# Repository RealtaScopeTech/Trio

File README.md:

# Trio
Realta Scope Tech: Trio Focuser

# What is it?

The REALTA Trio is a device that can control dew heaters, distribute 12 volt power and is an ASCOM compatible focuser. 

# Why did you make it?

The cost of some auxiliary astronomy equipment is crazy. I had no intention of paying $100 for a device the controls dew heaters via simple pulse width modulation, another $100 on a box that connects red and black wires to distribute 12v power and $200+ on a focuser controller. The cost saving plus the potential to learn something really intrigued me and the amount of information/free tools and general advice available to help people make things really inspired me, it's just astounding how useful the internet and open source/hardware have become. 

I also wanted to design something that fitted in a neat case as other maker options had a distinct DIY look to them, I wanted something that looked finished.

# License

Please feel free to make your own copies of the board/cases and ammend their design. Please give credit.

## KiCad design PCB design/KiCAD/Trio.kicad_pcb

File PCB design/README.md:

# PCB Design

The files used to design the PCB can be found in the KiCAD folder.

You may get issues with KiCAD not being able to find custom footprints and 3D models. We have placed all of those used within the KiCAD Extra's folder.

The "Production Files" folder contains all the files need to manufacture the PCB. It includes the Gerber files and a SMD position file and BOM file that can be used with JLCPCB to manufature a board with the SMD components included.

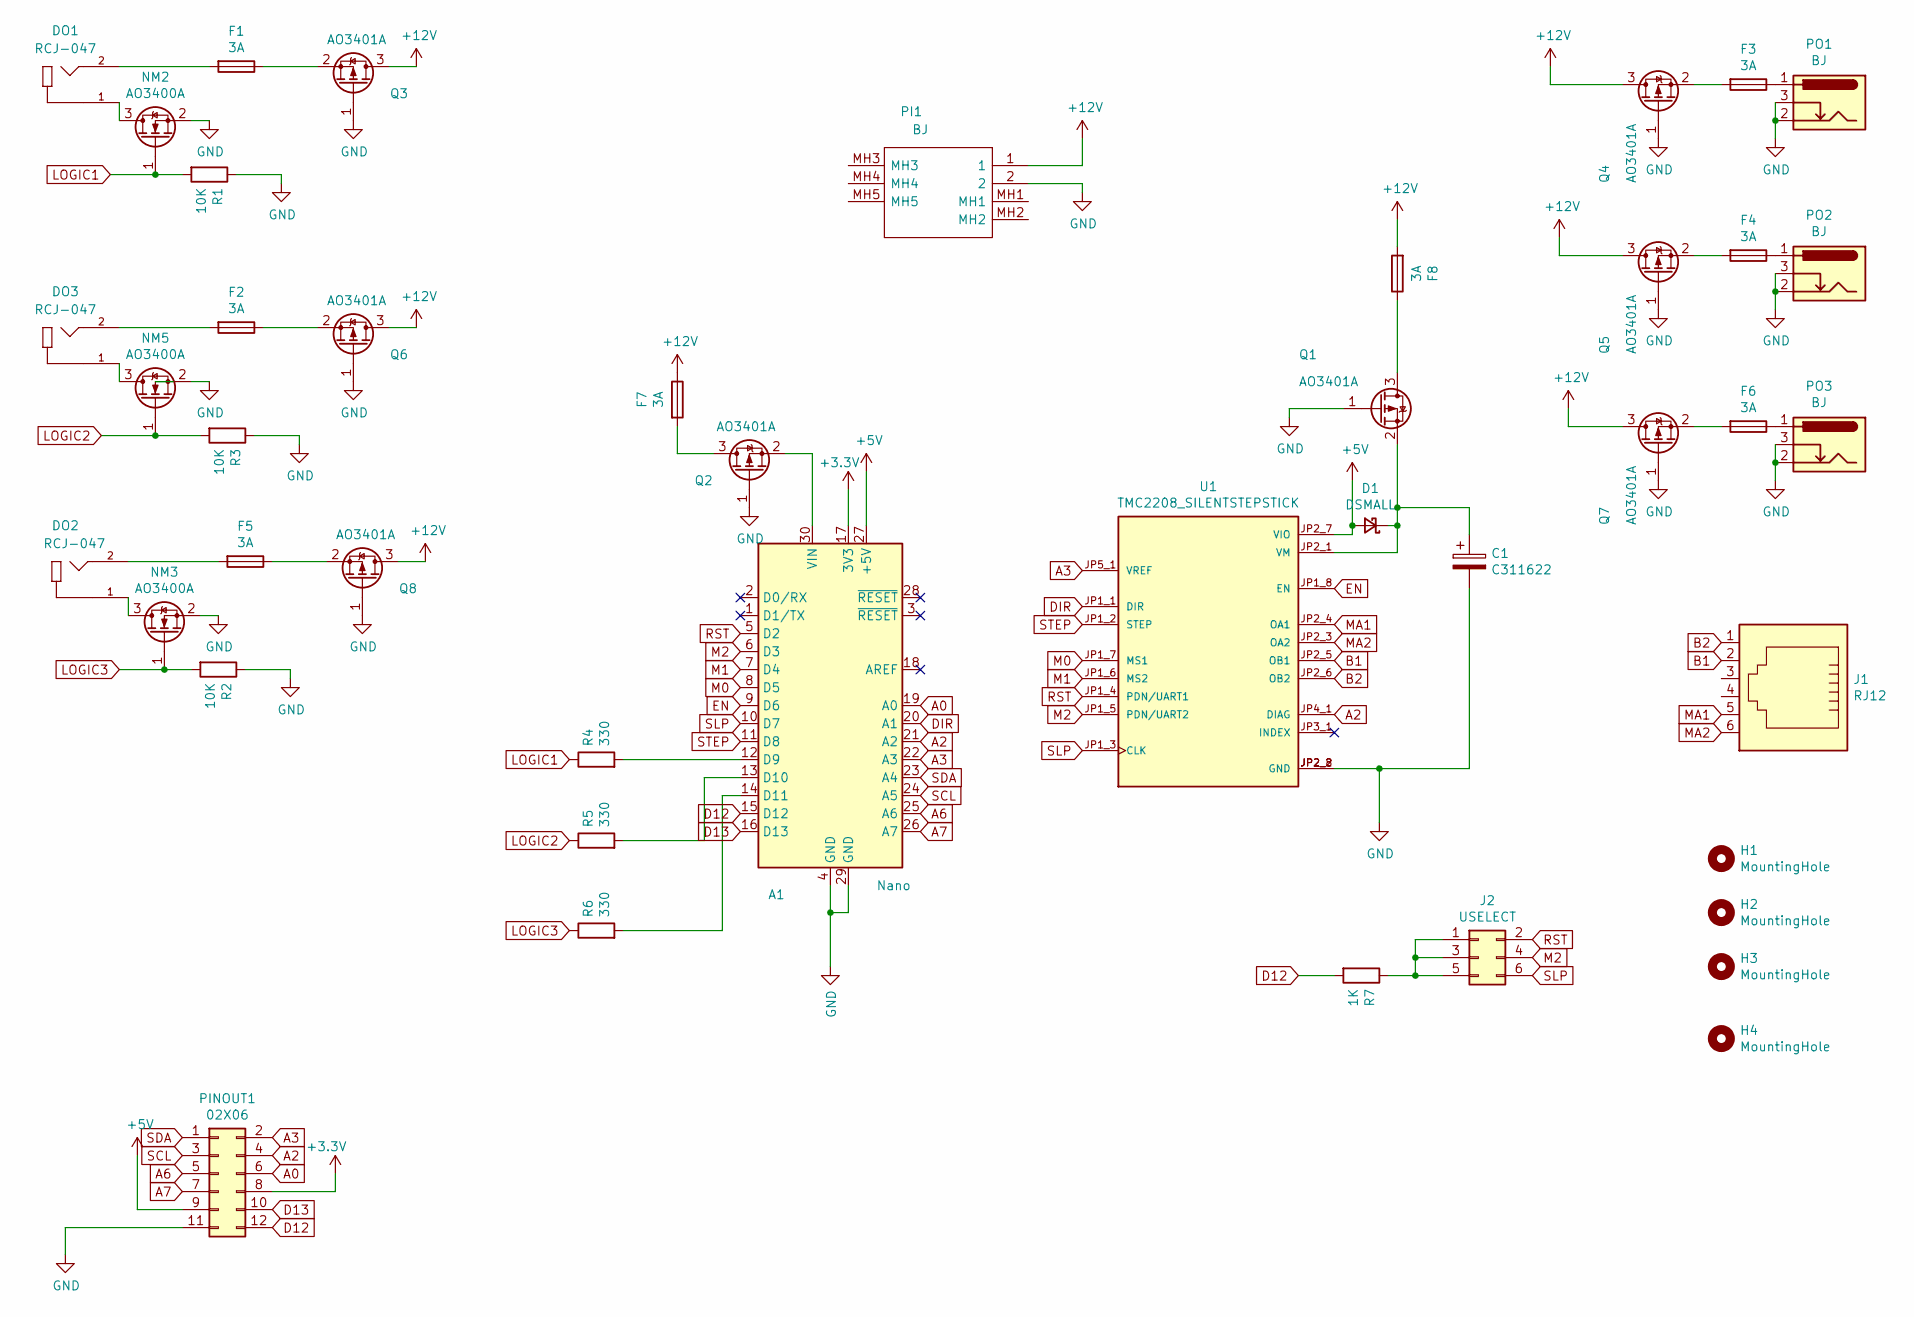
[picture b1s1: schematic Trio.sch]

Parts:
A1: Nano; Arduino_Nano
C1: C311622; CP_Elec_6.3x7.7; LCSC Part # C311622
D1: DSMALL; D_SOD-123; LCSC Part # C8598
DO1, DO2, DO3: RCJ-047; CUI_RCJ-047
F1, F2, F3, F4, F5, F6, F7, F8: 3A; Fuse_1206_3216Metric; LCSC Part # C182445
H1, H2, H3, H4: MountingHole; MountingHole_2.2mm_M2
J1: RJ12; RJ12_Amphenol_54601
J2: USELECT; PinHeader_2x03_P2.54mm_Vertical
NM2, NM3, NM5: AO3400A; SOT-23; LCSC Part # C20917
PI1: BJ; FC681495
PINOUT1: 02X06; PinHeader_2x06_P2.54mm_Vertical
PO1, PO2, PO3: BJ; BarrelJack_Wuerth_6941xx301002
Q1, Q2, Q3, Q4, Q5, Q6, Q7, Q8: AO3401A; SOT-23; LCSC Part # C15127
R1, R2, R3: 10K; R_0805_2012Metric; LCSC Part # C17414
R4, R5, R6: 330; R_0805_2012Metric; LCSC Part # C17630
R7: 1K; R_0805_2012Metric; LCSC Part # C17513
U1: TMC2208_SILENTSTEPSTICK; MODULE_TMC2208_SILENTSTEPSTICK; PARTREV v11

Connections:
+3V3: A1.17 (3V3), PINOUT1.8
+5V: A1.27 (+5V), D1.2 (A), PINOUT1.9, U1.JP2_7 (VIO)
+12V: F7.1, F8.2, PI1.1, Q3.3 (D), Q4.3 (D), Q5.3 (D), Q6.3 (D), Q7.3 (D), Q8.3 (D)
A0: A1.19 (A0), PINOUT1.6
A2: A1.21 (A2), PINOUT1.4, U1.JP4_1 (DIAG)
A3: A1.22 (A3), PINOUT1.2, U1.JP5_1 (VREF)
A6: A1.25 (A6), PINOUT1.5
A7: A1.26 (A7), PINOUT1.7
B1: J1.2, U1.JP2_5 (OB1)
B2: J1.1, U1.JP2_6 (OB2)
D12: A1.15 (D12), PINOUT1.12, R7.2
D13: A1.16 (D13), PINOUT1.10
DIR: A1.20 (A1), U1.JP1_1 (DIR)
EN: A1.9 (D6), U1.JP1_8 (EN)
GND: A1.4 (GND), A1.29 (GND), C1.2, NM2.2 (S), NM3.2 (S), NM5.2 (S), PI1.2, PINOUT1.11, PO1.2, PO1.3, PO2.2, PO2.3, PO3.2, PO3.3, Q1.1 (G), Q2.1 (G), Q3.1 (G), Q4.1 (G), Q5.1 (G), Q6.1 (G), Q7.1 (G), Q8.1 (G), R1.1, R2.1, R3.1, U1.JP2_2 (GND), U1.JP2_8 (GND)
LOGIC1: NM2.1 (G), R1.2, R4.1
LOGIC2: NM5.1 (G), R3.2, R5.1
LOGIC3: NM3.1 (G), R2.2, R6.1
M0: A1.8 (D5), U1.JP1_7 (MS1)
M1: A1.7 (D4), U1.JP1_6 (MS2)
M2: A1.6 (D3), J2.4, U1.JP1_5 (PDN/UART2)
MA1: J1.5, U1.JP2_4 (OA1)
MA2: J1.6, U1.JP2_3 (OA2)
unnamed: A1.12 (D9), R4.2
unnamed: A1.13 (D10), R5.2
unnamed: A1.14 (D11), R6.2
unnamed: A1.30 (VIN), Q2.2 (S)
unnamed: C1.1, D1.1 (K), Q1.2 (S), U1.JP2_1 (VM)
unnamed: DO1.1, NM2.3 (D)
unnamed: DO1.2, F1.2
unnamed: DO2.1, NM3.3 (D)
unnamed: DO2.2, F5.2
unnamed: DO3.1, NM5.3 (D)
unnamed: DO3.2, F2.2
unnamed: F1.1, Q3.2 (S)
unnamed: F2.1, Q6.2 (S)
unnamed: F3.1, PO1.1
unnamed: F3.2, Q4.2 (S)
unnamed: F4.1, PO2.1
unnamed: F4.2, Q5.2 (S)
unnamed: F5.1, Q8.2 (S)
unnamed: F6.1, PO3.1
unnamed: F6.2, Q7.2 (S)
unnamed: F7.2, Q2.3 (D)
unnamed: F8.1, Q1.3 (D)
unnamed: J2.1, J2.3, J2.5, R7.1
RST: A1.5 (D2), J2.2, U1.JP1_4 (PDN/UART1)
SCL: A1.24 (A5), PINOUT1.3
SDA: A1.23 (A4), PINOUT1.1
SLP: A1.10 (D7), J2.6, U1.JP1_3 (CLK)
STEP: A1.11 (D8), U1.JP1_2 (STEP)

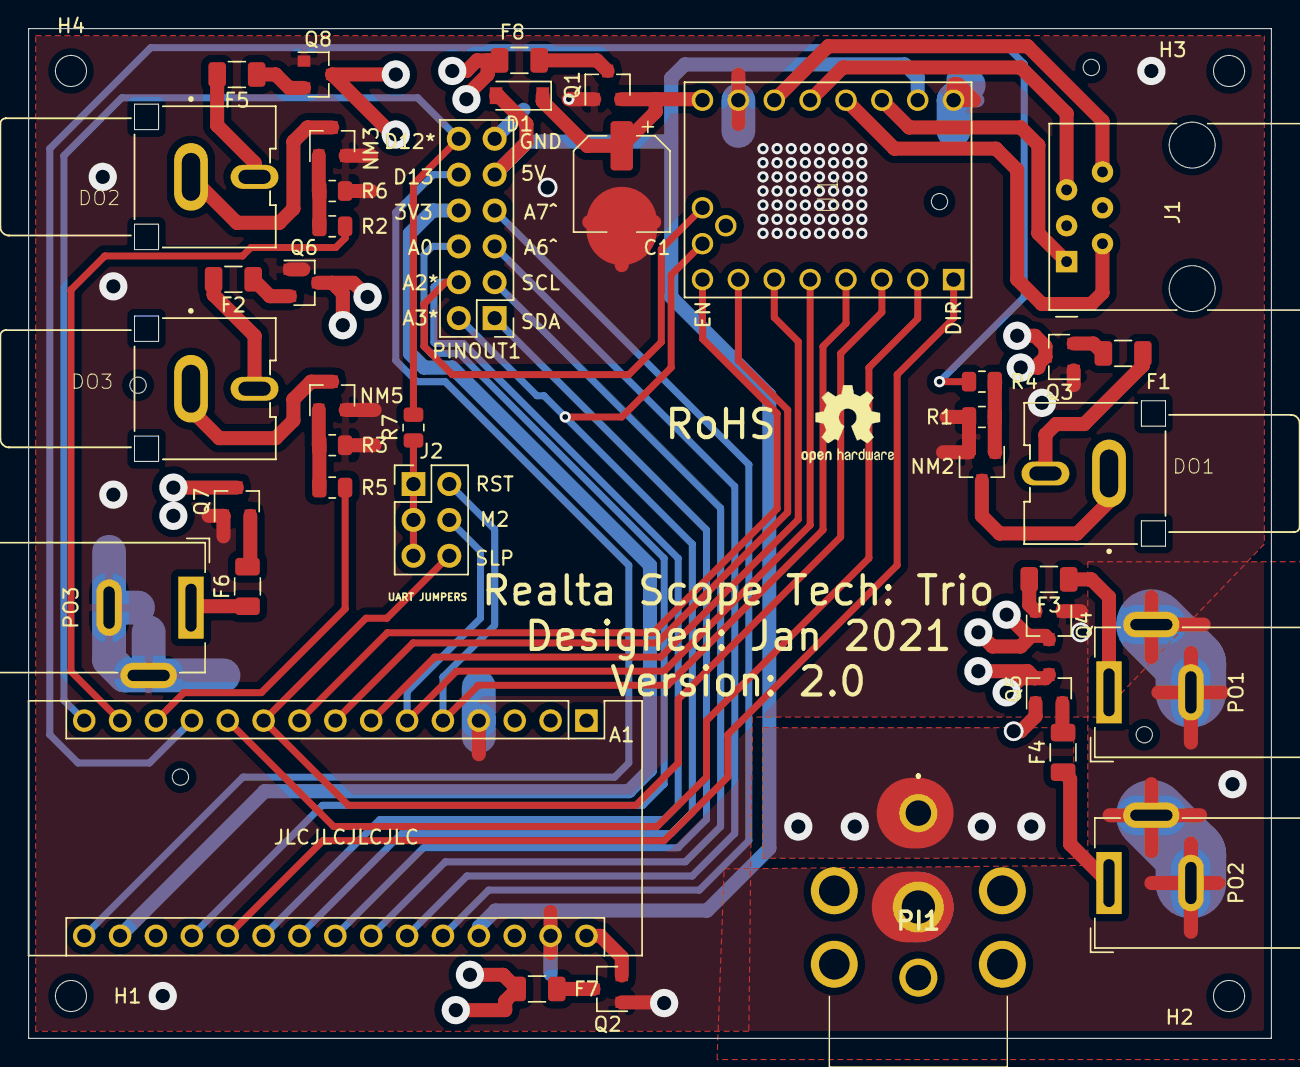
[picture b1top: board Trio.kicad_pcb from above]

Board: 4 copper layers, 88.0 x 71.5 mm, 44 parts (0 on the bottom side), 51 nets.

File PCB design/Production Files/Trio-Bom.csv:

Comment,Designator,Footprint,LCSC
"C311622","C1","Capacitor_SMD:CP_Elec_6.3x7.7","C311622"
"DSMALL","D1","Diode_SMD:D_SOD-123","C8598"
"3A","F1,F2,F3,F4,F5,F6,F7,F8","Fuse:Fuse_1206_3216Metric","C182445"
"AO3400A","NM2,NM3,NM5","Package_TO_SOT_SMD:SOT-23","C20917"
"AO3401A","Q1,Q2,Q3,Q4,Q5,Q6,Q7,Q8","Package_TO_SOT_SMD:SOT-23","C15127"
"10K","R1,R2,R3","Resistor_SMD:R_0805_2012Metric","C17414"
"330","R4,R5,R6","Resistor_SMD:R_0805_2012Metric","C17630"
"1K","R7","Resistor_SMD:R_0805_2012Metric","C17513"

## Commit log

2021-04-13 Rename DRV8825/Readme.txt to Software/DRV8825/Readme.txt
2021-04-13 Create Windows
2021-04-14 Add files via upload
    Added saving of user settings
2021-04-14 Added saving of user settings
    Added saving of user settings
2021-04-14 Removed network test features
    Removed network test features and added saving of focuser position
2021-04-14 Rounded temperature and humidity
    Rounded temperature and humidity
2021-04-20 Increased allowed focuser positions
    Increased allowed focuser positions from 100,000 to 1,000,000
2021-04-22 Uploaded files to wrong directory
    Uploaded files to wrong directory
2021-04-24 No longer needs windows app to be running
    No longer needs windows app to be running
